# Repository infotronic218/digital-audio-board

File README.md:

# Digital Audio board design and software development

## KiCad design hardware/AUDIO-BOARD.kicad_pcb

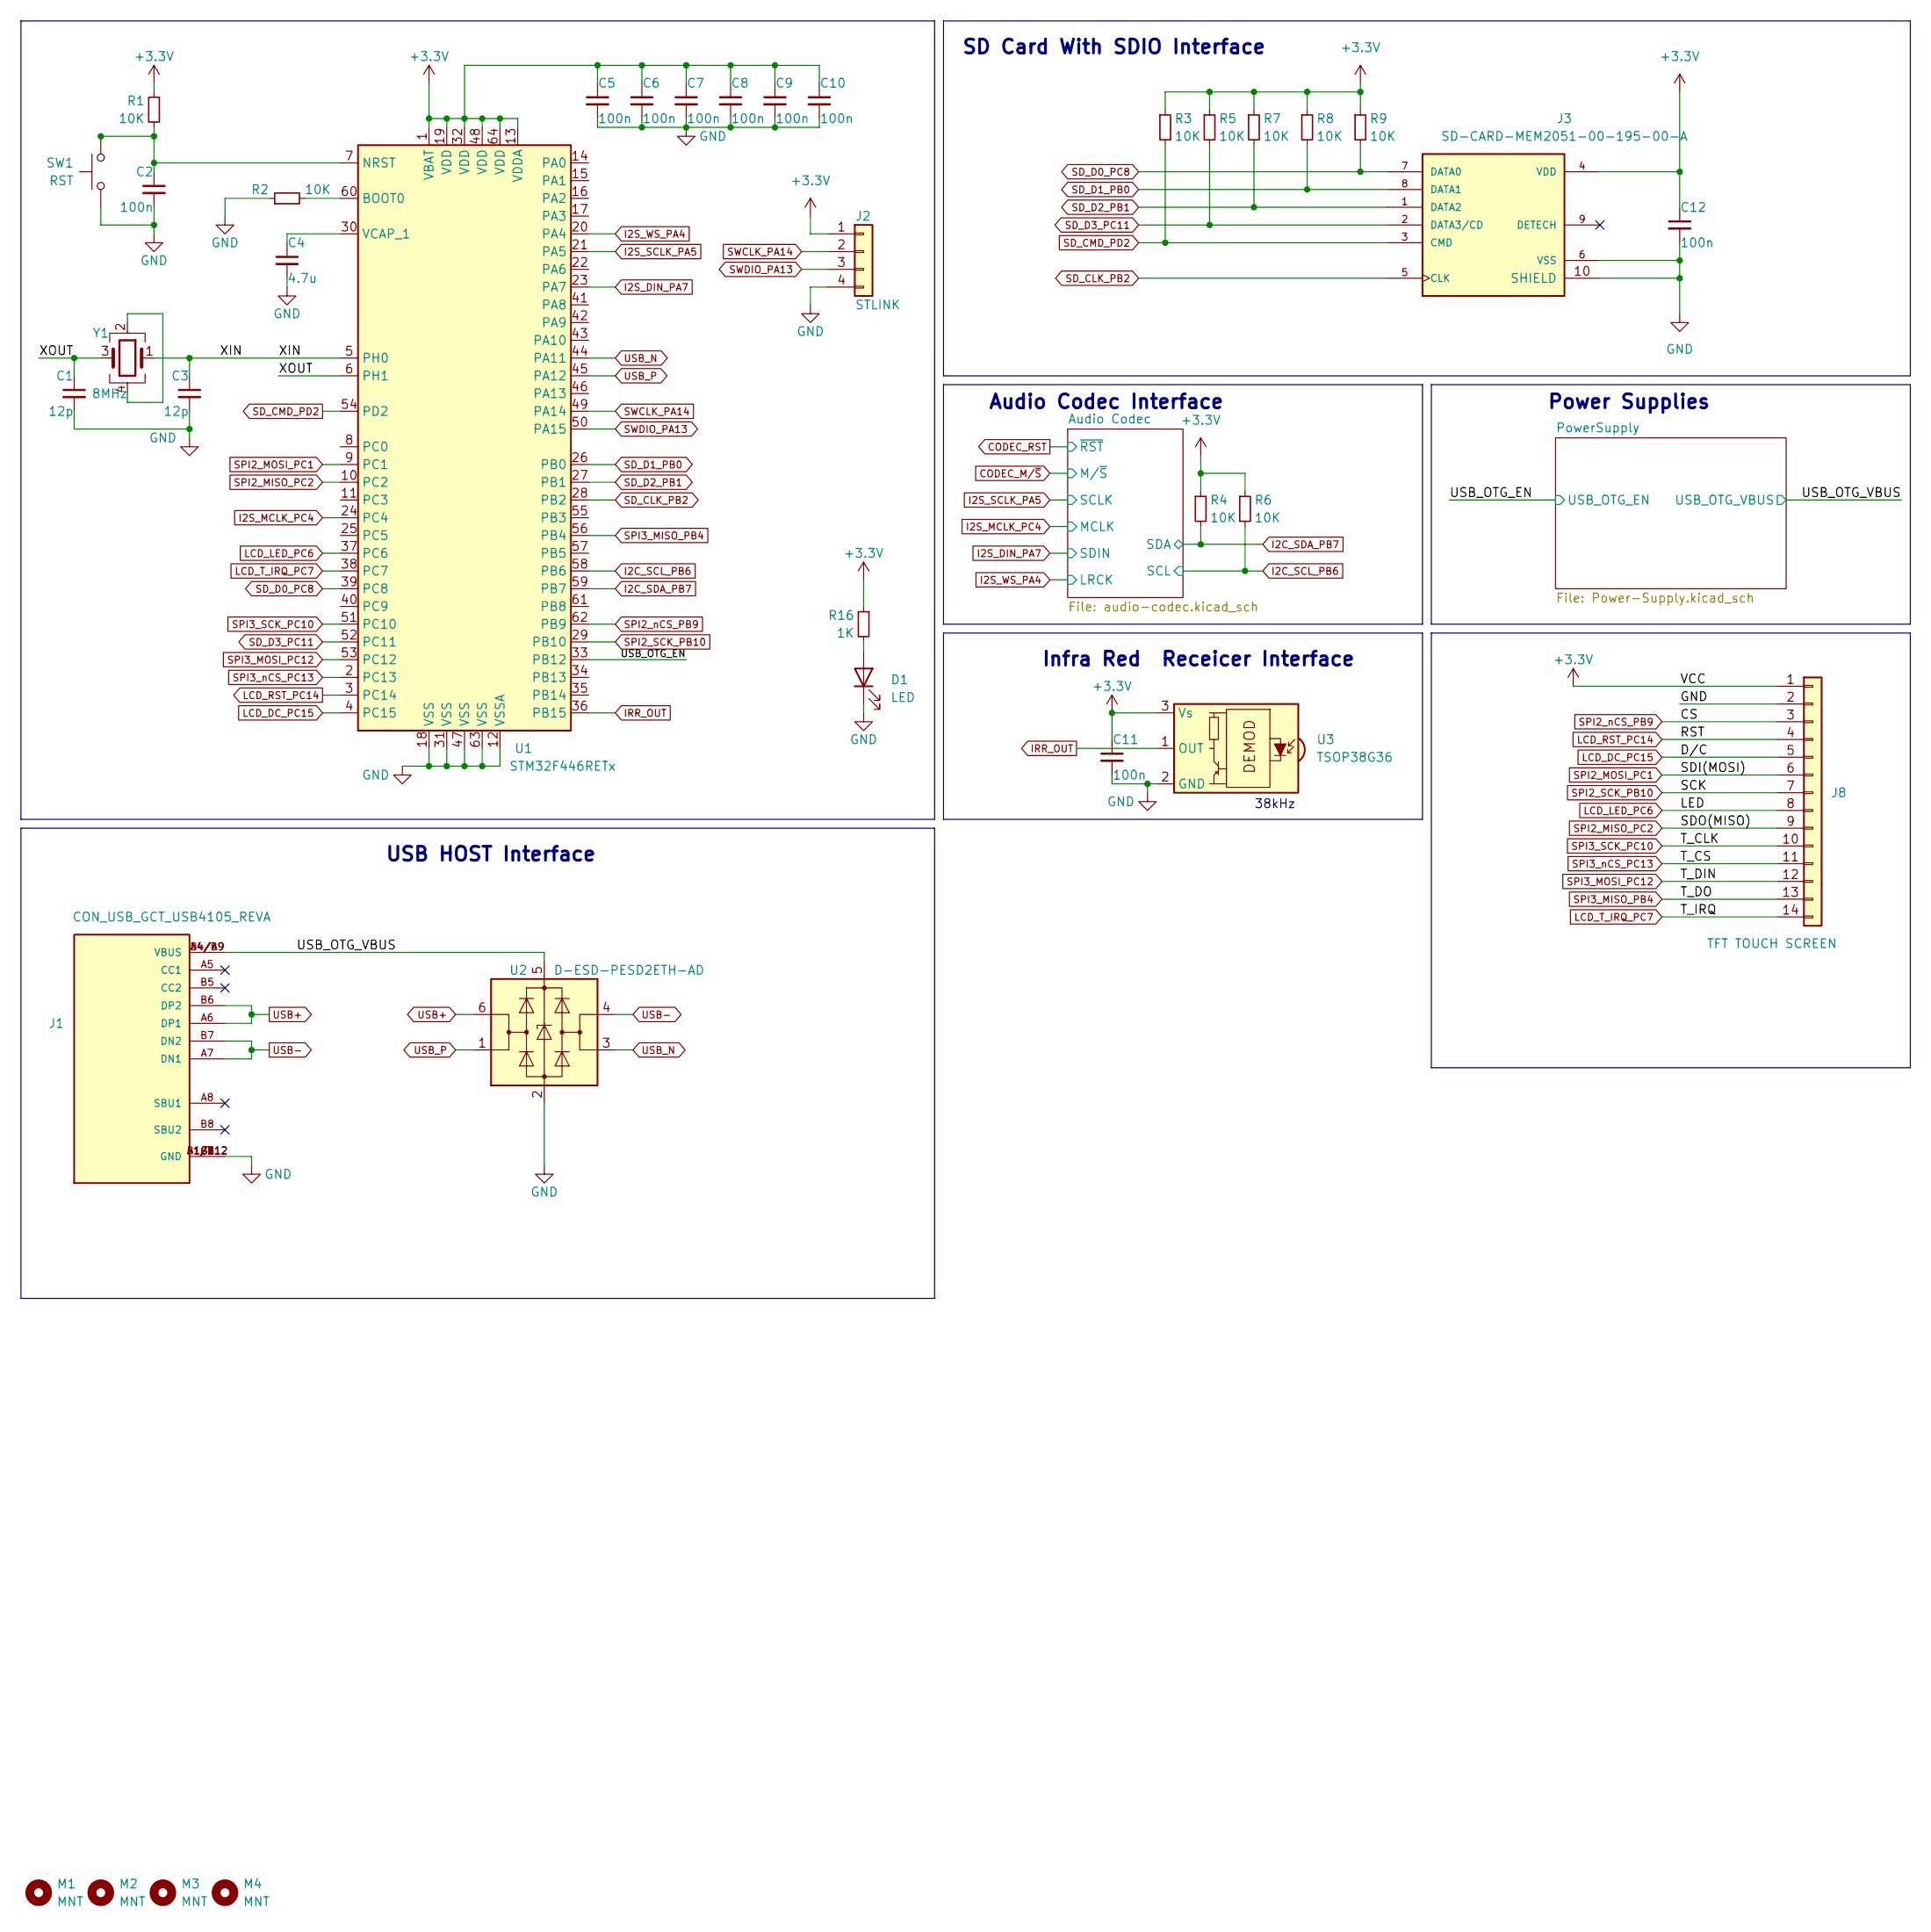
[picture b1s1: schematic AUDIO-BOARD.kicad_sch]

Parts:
C1, C3: 12p; C_0603_1608Metric
C2, C5, C6, C7, C8, C9, C10, C11, C12: 100n; C_0603_1608Metric
C4: 4.7u; C_0805_2012Metric
D1: LED; LED_0805_2012Metric
J1: CON_USB_GCT_USB4105_REVA; PARTREV 0.2
J2: STLINK; PinHeader_1x04_P2.54mm_Vertical
J3: SD-CARD-MEM2051-00-195-00-A; MPN MEM2051-00-195-00-A; Mouser 640-MEM20510019500A
J8: TFT TOUCH SCREEN; PinSocket_1x14_P2.54mm_Vertical
M1, M2, M3, M4: MNT; MountingHole_2.1mm
R1, R2, R3, R4, R5, R6, R7, R8, R9: 10K; R_0805_2012Metric
R16: 1K; R_0805_2012Metric
SW1: RST; SW_SPST_B3U-1000P-B
U1: STM32F446RETx; LQFP-64_10x10mm_P0.5mm
U2: D-ESD-PESD2ETH-AD; SOT-23-6
U3: TSOP38G36; Vishay_MINICAST-3Pin
Y1: 8MHz; Crystal_SMD_3225-4Pin_3.2x2.5mm

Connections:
+3.3V: C5.1, C6.1, C7.1, C8.1, C9.1, C10.1, C11.1, C12.1, J2.1, J3.4 (VDD), J8.1, R1.1, R3.1, R4.1, R5.1, R6.1, R7.1, R8.1, R9.1, R16.1, U1.1 (VBAT), U1.13 (VDDA), U1.19 (VDD), U1.32 (VDD), U1.48 (VDD), U1.64 (VDD), U3.3 (Vs); also elsewhere on the board
/USB_OTG_EN: U1.33 (PB12); also elsewhere on the board
/USB_OTG_VBUS: J1.A4/B9 (VBUS), J1.B4/A9 (VBUS), U2.5 (VBUS); also elsewhere on the board
/XIN: C3.1, U1.5 (PH0), Y1.1
/XOUT: C1.1, U1.6 (PH1), Y1.3
GND: C1.2, C2.2, C3.2, C4.2, C5.2, C6.2, C7.2, C8.2, C9.2, C10.2, C11.2, C12.2, D1.1 (K), J1.A1/B12 (GND), J1.B1/A12 (GND), J1.G1 (GND), J1.G2 (GND), J1.G3 (GND), J1.G4 (GND), J2.4, J3.6 (VSS), J3.10 (SHIELD), J8.2, R2.1, SW1.2, U1.12 (VSSA), U1.18 (VSS), U1.31 (VSS), U1.47 (VSS), U1.63 (VSS), U2.2 (GND), U3.2 (GND); also elsewhere on the board
I2C_SCL_PB6: R6.2, U1.58 (PB6); also elsewhere on the board
I2C_SDA_PB7: R4.2, U1.59 (PB7); also elsewhere on the board
I2S_DIN_PA7: U1.23 (PA7); also elsewhere on the board
I2S_MCLK_PC4: U1.24 (PC4); also elsewhere on the board
I2S_SCLK_PA5: U1.21 (PA5); also elsewhere on the board
I2S_WS_PA4: U1.20 (PA4); also elsewhere on the board
IRR_OUT: U1.36 (PB15), U3.1 (OUT)
LCD_DC_PC15: J8.5, U1.4 (PC15)
LCD_LED_PC6: J8.8, U1.37 (PC6)
LCD_RST_PC14: J8.4, U1.3 (PC14)
LCD_T_IRQ_PC7: J8.14, U1.38 (PC7)
unnamed: D1.2 (A), R16.2
unnamed: R2.2, U1.60 (BOOT0)
unnamed: C2.1, R1.2, SW1.1, U1.7 (NRST)
unnamed: C4.1, U1.30 (VCAP_1)
unnamed: Y1.2, Y1.4
SD_CLK_PB2: J3.5 (CLK), U1.28 (PB2)
SD_CMD_PD2: J3.3 (CMD), R3.2, U1.54 (PD2)
SD_D0_PC8: J3.7 (DATA0), R9.2, U1.39 (PC8)
SD_D1_PB0: J3.8 (DATA1), R8.2, U1.26 (PB0)
SD_D2_PB1: J3.1 (DATA2), R7.2, U1.27 (PB1)
SD_D3_PC11: J3.2 (DATA3/CD), R5.2, U1.52 (PC11)
SPI2_MISO_PC2: J8.9, U1.10 (PC2)
SPI2_MOSI_PC1: J8.6, U1.9 (PC1)
SPI2_SCK_PB10: J8.7, U1.29 (PB10)
SPI2_nCS_PB9: J8.3, U1.62 (PB9)
SPI3_MISO_PB4: J8.13, U1.56 (PB4)
SPI3_MOSI_PC12: J8.12, U1.53 (PC12)
SPI3_SCK_PC10: J8.10, U1.51 (PC10)
SPI3_nCS_PC13: J8.11, U1.2 (PC13)
SWCLK_PA14: J2.2, U1.49 (PA14)
SWDIO_PA13: J2.3, U1.50 (PA15)
USB+: J1.A6 (DP1), J1.B6 (DP2), U2.6 (I/O1)
USB-: J1.A7 (DN1), J1.B7 (DN2), U2.4 (I/O2)
USB_N: U1.44 (PA11), U2.3 (I/O2)
USB_P: U1.45 (PA12), U2.1 (I/O1)

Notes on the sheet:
USB HOST Interface
SD Card With SDIO Interface
Power Supplies
Infra Red Receicer Interface
38kHz
Audio Codec Interface

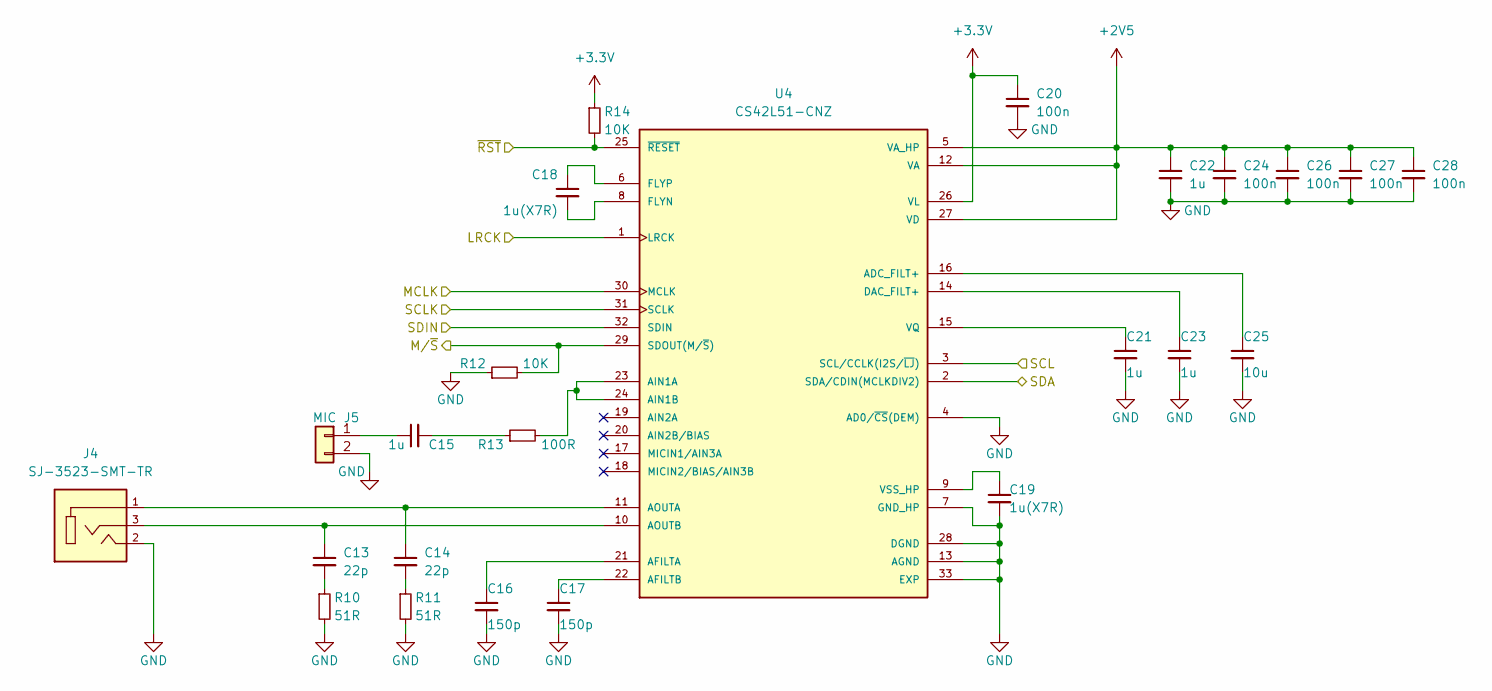
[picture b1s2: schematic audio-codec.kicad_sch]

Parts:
C13, C14: 22p; C_0603_1608Metric
C15, C21, C22, C23: 1u; C_0805_2012Metric
C16, C17: 150p; C_0603_1608Metric
C18, C19: 1u(X7R); C_0603_1608Metric
C20, C24, C26, C27, C28: 100n; C_0603_1608Metric
C25: 10u; C_0805_2012Metric
J4: SJ-3523-SMT-TR; CUI_SJ-3523-SMT-TR
J5: MIC; PinSocket_1x02_P2.54mm_Vertical
R10, R11: 51R; R_0805_2012Metric
R12, R14: 10K; R_0805_2012Metric
R13: 100R; R_0805_2012Metric
U4: CS42L51-CNZ; QFN-32-1EP_5x5mm_P0.5mm_EP3.1x3.1mm

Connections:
+2V5: C22.1, C24.1, C26.1, C27.1, C28.1, U4.5 (VA_HP), U4.12 (VA), U4.27 (VD); also elsewhere on the board
+3.3V: C20.1, R14.1, U4.26 (VL); also elsewhere on the board
CODEC_M/~S: R12.2, U4.29 (SDOUT(M/~S))
CODEC_RST: R14.2, U4.25 (~RESET)
GND: C16.2, C17.2, C19.2, C20.2, C21.2, C22.2, C23.2, C24.2, C25.2, C26.2, C27.2, C28.2, J4.2, J5.2, R10.2, R11.2, R12.1, U4.4 (AD0/~CS(DEM)), U4.7 (GND_HP), U4.13 (AGND), U4.28 (DGND), U4.33 (EXP); also elsewhere on the board
I2C_SCL_PB6: U4.3 (SCL/CCLK(I2S/~LJ)); also elsewhere on the board
I2C_SDA_PB7: U4.2 (SDA/CDIN(MCLKDIV2)); also elsewhere on the board
I2S_DIN_PA7: U4.32 (SDIN); also elsewhere on the board
I2S_MCLK_PC4: U4.30 (MCLK); also elsewhere on the board
I2S_SCLK_PA5: U4.31 (SCLK); also elsewhere on the board
I2S_WS_PA4: U4.1 (LRCK); also elsewhere on the board
unnamed: C13.2, R10.1
unnamed: C14.2, R11.1
unnamed: C15.2, R13.1
unnamed: C15.1, J5.1
unnamed: C25.1, U4.16 (ADC_FILT+)
unnamed: C16.1, U4.21 (AFILTA)
unnamed: C17.1, U4.22 (AFILTB)
unnamed: R13.2, U4.23 (AIN1A), U4.24 (AIN1B)
unnamed: C14.1, J4.1, U4.11 (AOUTA)
unnamed: C13.1, J4.3, U4.10 (AOUTB)
unnamed: C23.1, U4.14 (DAC_FILT+)
unnamed: C18.2, U4.8 (FLYN)
unnamed: C18.1, U4.6 (FLYP)
unnamed: C21.1, U4.15 (VQ)
unnamed: C19.1, U4.9 (VSS_HP)

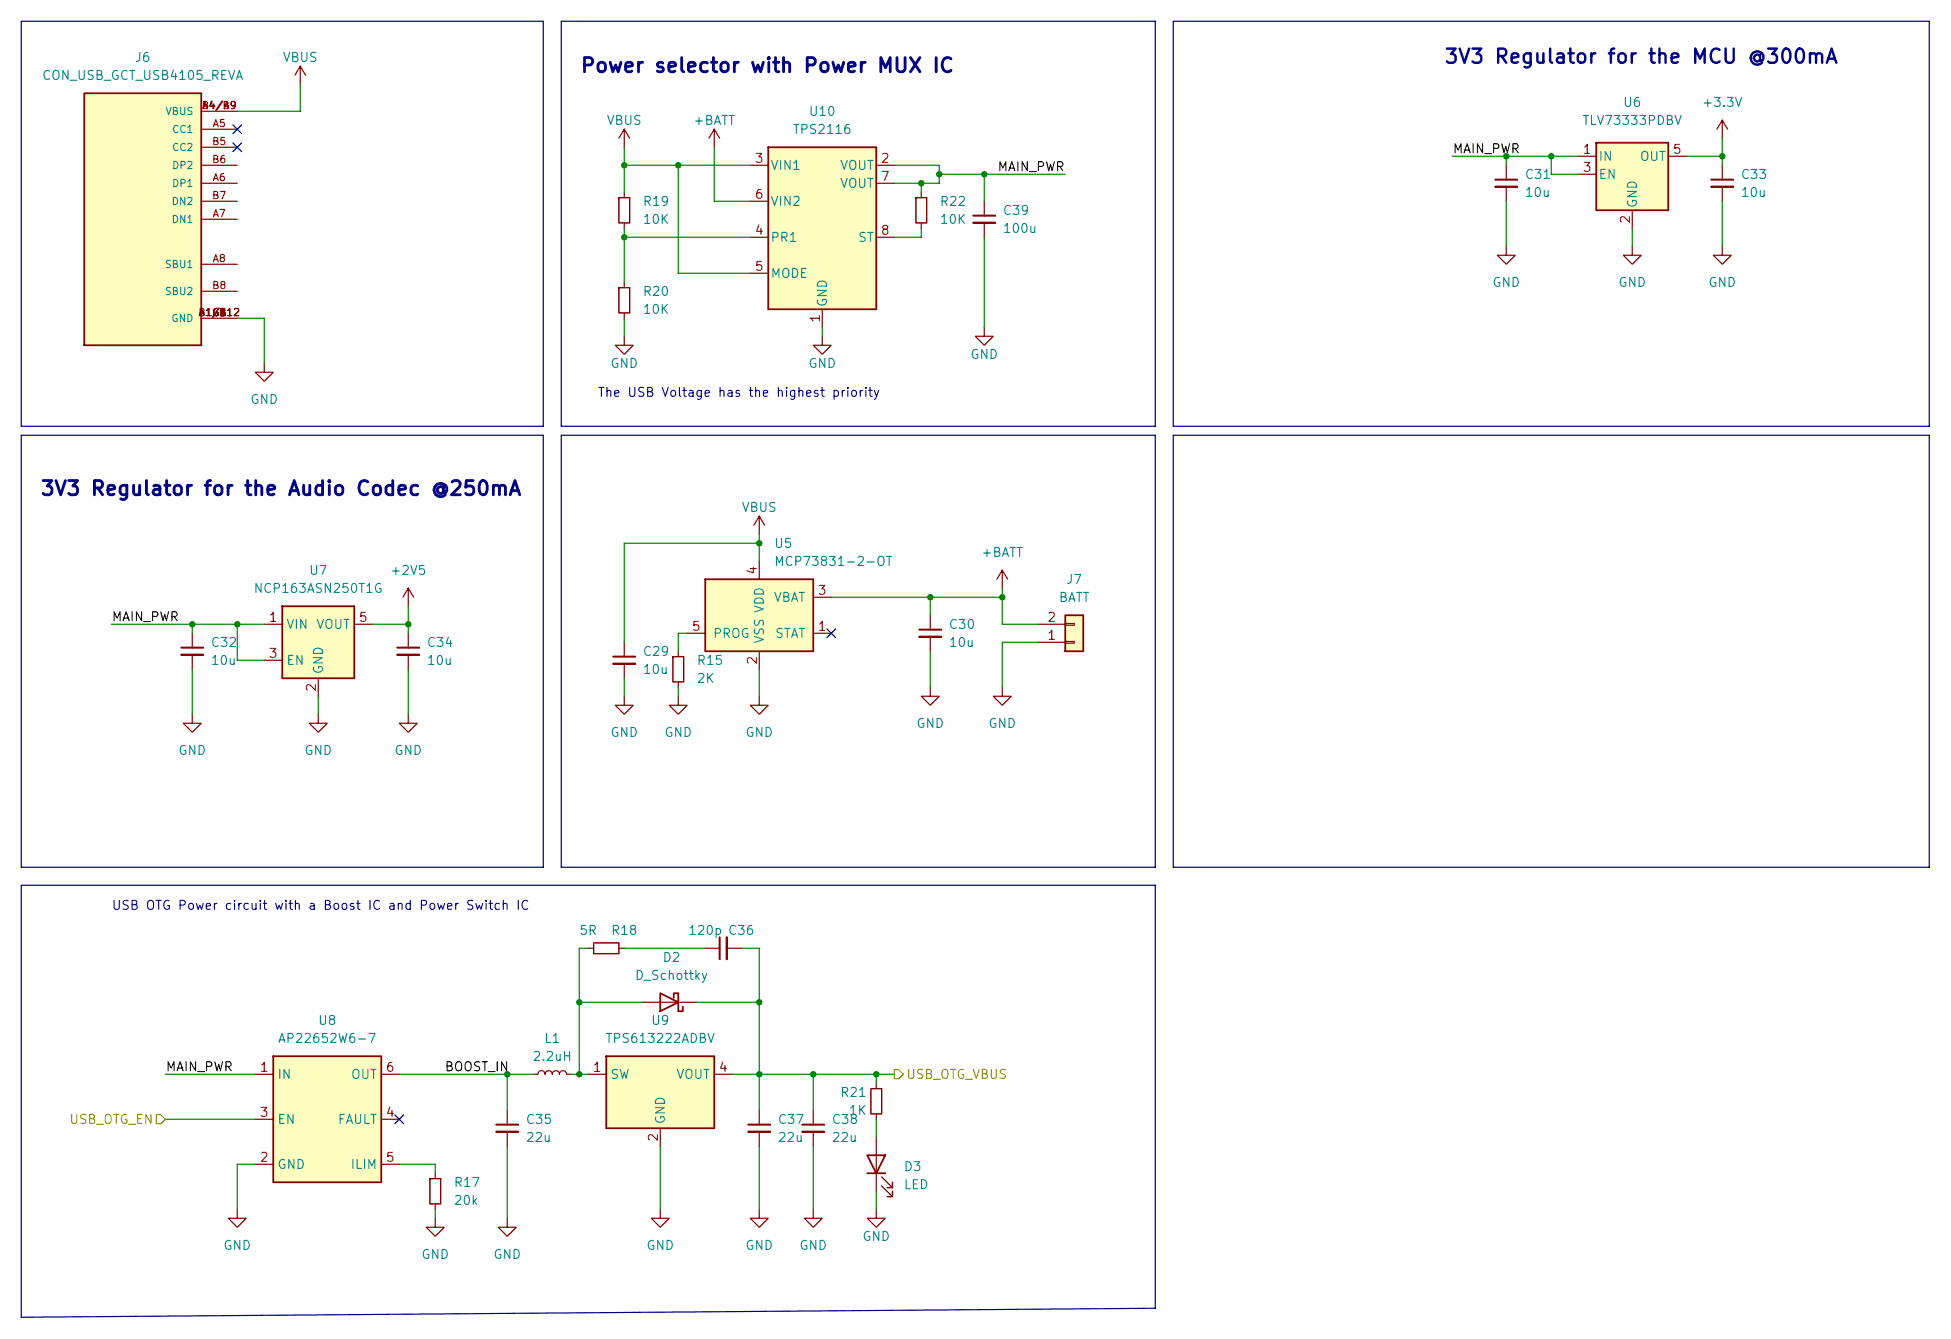
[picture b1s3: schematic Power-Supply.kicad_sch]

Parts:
C29, C30, C31, C32, C33, C34: 10u; C_0805_2012Metric
C35, C37, C38: 22u; C_0805_2012Metric
C36: 120p; C_0805_2012Metric
C39: 100u; C_0805_2012Metric
D2: D_Schottky; D_SOD-123
D3: LED; LED_0805_2012Metric
J6: CON_USB_GCT_USB4105_REVA; PARTREV 0.2
J7: BATT; JST_EH_B2B-EH-A_1x02_P2.50mm_Vertical
L1: 2.2uH; L_2010_5025Metric
R15: 2K; R_0805_2012Metric
R17: 20k; R_0805_2012Metric
R18: 5R; D_0805_2012Metric
R19, R20, R22: 10K; R_0805_2012Metric
R21: 1K; R_0805_2012Metric
U5: MCP73831-2-OT; SOT-23-5
U6: TLV73333PDBV; SOT-23-5
U7: NCP163ASN250T1G; SOT-23-5
U8: AP22652W6-7; SOT-23-6
U9: TPS613222ADBV; SOT-23-5
U10: TPS2116; SOT-23-8

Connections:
+2V5: C34.1, U7.5 (VOUT); also elsewhere on the board
+3.3V: C33.1, U6.5 (OUT); also elsewhere on the board
+BATT: C30.1, J7.2, U5.3 (VBAT), U10.6 (VIN2)
/PowerSupply/BOOST_IN: C35.1, L1.1, U8.6 (OUT)
/PowerSupply/MAIN_PWR: C31.1, C32.1, C39.1, R22.1, U6.1 (IN), U6.3 (EN), U7.1 (VIN), U7.3 (EN), U8.1 (IN), U10.2 (VOUT), U10.7 (VOUT)
/USB_OTG_EN: U8.3 (EN); also elsewhere on the board
/USB_OTG_VBUS: C36.2, C37.1, C38.1, D2.1 (K), R21.1, U9.4 (VOUT); also elsewhere on the board
GND: C29.2, C30.2, C31.2, C32.2, C33.2, C34.2, C35.2, C37.2, C38.2, C39.2, D3.1 (K), J6.A1/B12 (GND), J6.B1/A12 (GND), J6.G1 (GND), J6.G2 (GND), J6.G3 (GND), J6.G4 (GND), J7.1, R15.2, R17.2, R20.2, U5.2 (VSS), U6.2 (GND), U7.2 (GND), U8.2 (GND), U9.2 (GND), U10.1 (GND); also elsewhere on the board
unnamed: C36.1, R18.2
unnamed: D2.2 (A), L1.2, R18.1, U9.1 (SW)
unnamed: D3.2 (A), R21.2
unnamed: R15.1, U5.5 (PROG)
unnamed: R17.1, U8.5 (ILIM)
unnamed: R19.2, R20.1, U10.4 (PR1)
unnamed: R22.2, U10.8 (ST)
VBUS: C29.1, J6.A4/B9 (VBUS), J6.B4/A9 (VBUS), R19.1, U5.4 (VDD), U10.3 (VIN1), U10.5 (MODE)

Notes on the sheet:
The USB Voltage has the highest priority
3V3 Regulator for the MCU @300mA
3V3 Regulator for the Audio Codec @250mA
USB OTG Power circuit with a Boost IC and Power Switch IC
Power selector with Power MUX IC

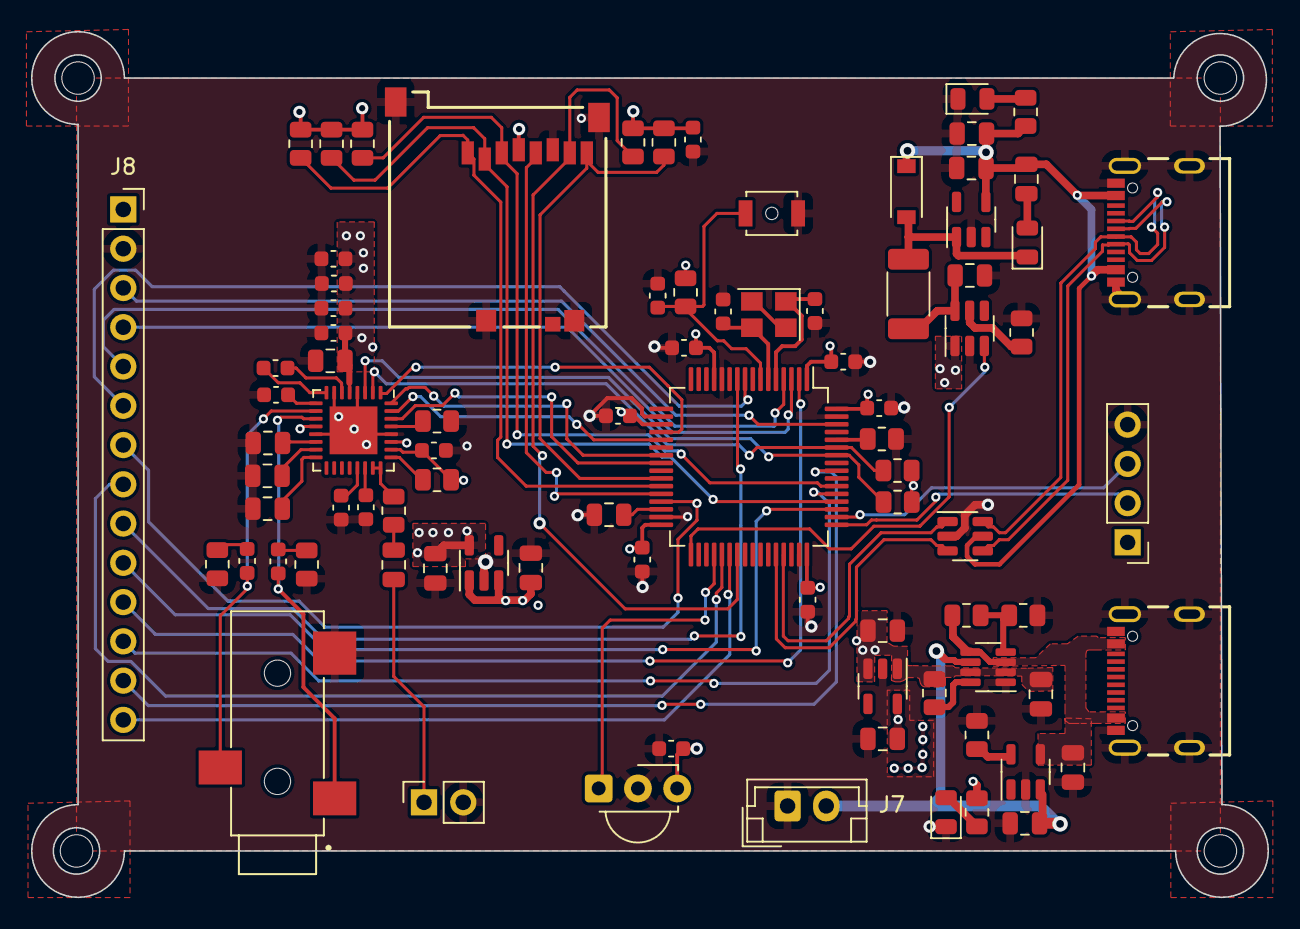
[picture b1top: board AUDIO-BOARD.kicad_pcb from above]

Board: 4 copper layers, 80.0 x 56.0 mm, 89 parts (0 on the bottom side), 71 nets.

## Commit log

2022-12-28 Project setup
2023-01-12 Updating the power section
2023-01-14 update the file
2023-01-22 update the design
2023-02-01 Update placements
2023-03-08 Update the PCB routing
